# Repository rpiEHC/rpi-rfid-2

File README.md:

# RPI RFID

The goal of RPI RFID is to design, build and test an RPI id card (HID Proxcard II) reader.

## Getting Started

After cloning the repo, execute the following commands to get all the libraries we use for the project.

`git submodule init` 
`git submodule update`

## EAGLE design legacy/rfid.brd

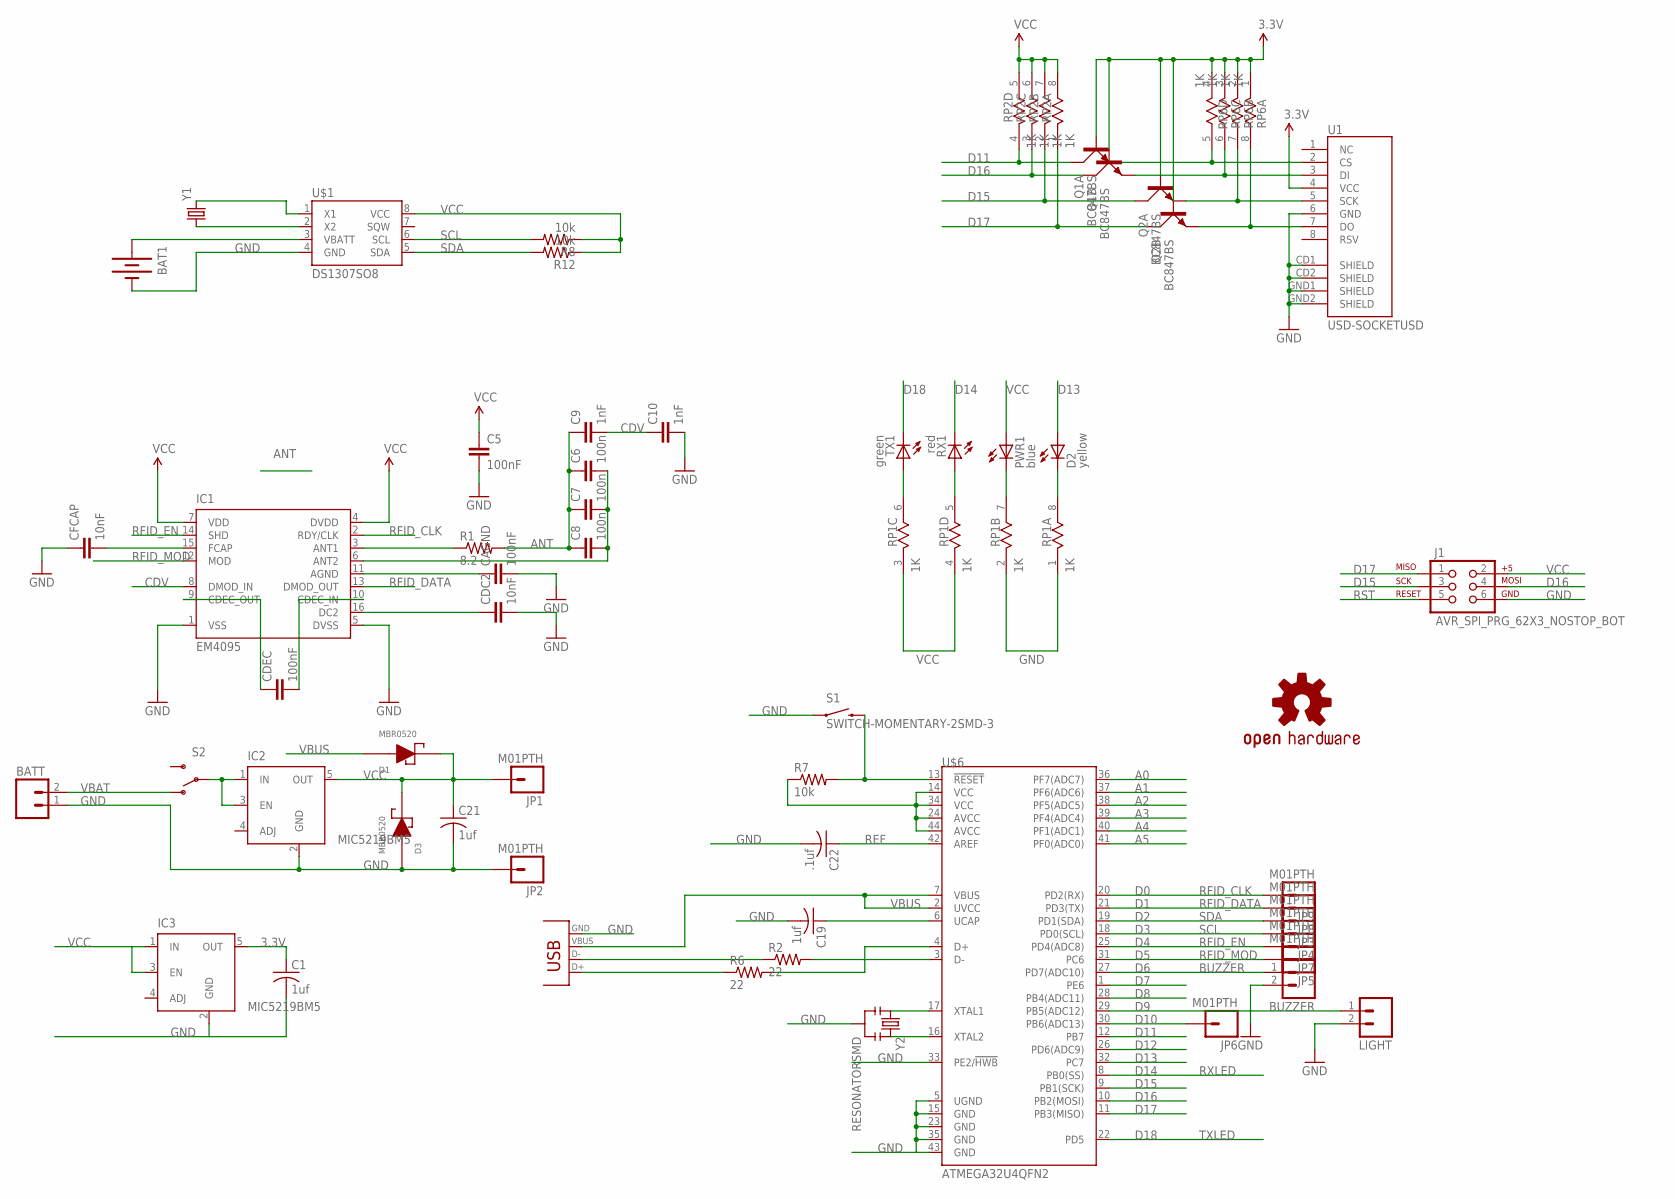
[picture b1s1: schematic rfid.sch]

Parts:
BAT1: BATTERY12MM; BATTCON_12MM
BATT: M02PTH; 1X02
BUZZER: M02PTH; 1X02
C1, C19, C21: 1uf; C0603
C5: 100nF; 0805
C6, C7, C8: 100n; 0805
C9, C10: 1nF; 0805
C22: .1uf; C0603
CAGND: 100nF; 0805
CDC2: 10nF; 0805
CDEC: 100nF; 0805
CFCAP: 10nF; 0805
D1, D3: MBR0520; SOD-123
D2: yellow; LED3MM
IC1: EM4095; SO16
IC2: MIC5219BM5; SOT23-5
IC3: MIC5219BM5; SOT23-5; MPN MIC5219BM5 TR
J1: AVR_SPI_PRG_62X3_NOSTOP_BOT; 2X3_STOP_BOT
JP1, JP2, JP3, JP4, JP5, JP6, JP7, JP8, JP9: M01PTH; 1X01
LIGHT: M02PTH; 1X02
PWR1: blue; LED3MM
Q1, Q2: BC847BS; SOT363_PHILIPS
R1: 8.2; 0805
R2, R6: 22; 0603-RES
R7, R8, R12: 10k; 0603-RES
RP1, RP2, RP6: 1K; RES4NT
RX1: red; LED3MM
S1: SWITCH-MOMENTARY-2SMD-3; TACTILE_SWITCH_SMD-3
S2: SWITCH-SPDT-SMD-A; SWITCH-SPST-SMD-A
TX1: green; LED3MM
U1: USD-SOCKETUSD; USD-SOCKET-PP
U$1: DS1307SO8; SO08
U$2: USB_MICROB; USB-MICROB
U$3: OSHW-LOGOL; OSHW-LOGO-L
U$6: ATMEGA32U4QFN2; QFN-44-NOPAD
Y1: CRYSTAL5X2; CRYSTAL-SMD-5X2
Y2: RESONATORSMD; RESONATOR-SMD

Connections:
3.3V: C1.1, IC3.5 (OUT), Q1.2 (B), Q1.5 (B), Q2.2 (B), Q2.5 (B), RP6.1, RP6.2 (1), RP6.3 (1), RP6.4 (1), U1.4 (VCC)
A0: U$6.36 (PF7(ADC7))
A1: U$6.37 (PF6(ADC6))
A2: U$6.38 (PF5(ADC5))
A3: U$6.39 (PF4(ADC4))
A4: U$6.40 (PF1(ADC1))
A5: U$6.41 (PF0(ADC0))
ANT: C6.1, C7.1, C8.1, C9.1, R1.2
CDV: C9.2, C10.1, IC1.8 (DMOD_IN)
D6: BUZZER.1, U$6.27 (PD7(ADC10))
D7: U$6.1 (PE6)
D8: U$6.28 (PB4(ADC11))
D9: LIGHT.1, U$6.29 (PB5(ADC12))
D10: JP6.1, U$6.30 (PB6(ADC13))
D11: Q1.6 (C), RP2.4 (1), U$6.12 (PB7)
D12: U$6.26 (PD6(ADC9))
D13: D2.A, U$6.32 (PC7)
D14: RX1.K (C), U$6.8 (PB0(SS))
D15: J1.3, Q2.6 (C), RP2.2 (1), U$6.9 (PB1(SCK))
D16: J1.4, Q1.3 (C), RP2.3 (1), U$6.10 (PB2(MOSI))
D17: J1.1, Q2.3 (C), RP2.1, U$6.11 (PB3(MISO))
D18: TX1.K (C), U$6.22 (PD5)
GND: BAT1.GND (-), BATT.1, BUZZER.2, C1.2, C5.2, C10.2, C19.2, C21.2, C22.2, CAGND.2, CDC2.2, CFCAP.1, D3.2 (AN), IC1.1 (VSS), IC1.5 (DVSS), IC2.2 (GND), IC3.2 (GND), J1.6, JP2.1, LIGHT.2, RP1.1, RP1.2 (1), S1.P$1 (1), U1.6 (GND), U1.CD1 (SHIELD), U1.CD2 (SHIELD), U1.GND1 (SHIELD), U1.GND2 (SHIELD), U$1.4 (GND), U$2.P4, U$2.P5, U$2.P$1, U$2.P$2, U$2.P$3, U$2.P$4, U$2.P$5, U$2.P$6, U$6.5 (UGND), U$6.15 (GND), U$6.23 (GND), U$6.33 (PE2/!HWB), U$6.35 (GND), U$6.43 (GND), Y2.2
unnamed: IC1.3 (ANT1), R1.1
unnamed: IC2.1 (IN), IC2.3 (EN), S2.2
unnamed: U$6.16 (XTAL2), Y2.3
unnamed: C6.2, C7.2, C8.2, IC1.6 (ANT2)
unnamed: Q1.4 (E), RP6.6 (2), U1.3 (DI)
unnamed: CAGND.1, IC1.11 (AGND)
unnamed: CDEC.2, IC1.10 (CDEC_IN)
unnamed: CDEC.1, IC1.9 (CDEC_OUT)
unnamed: Q2.1 (E), RP6.7 (2), U1.5 (SCK)
unnamed: Q2.4 (E), RP6.8 (2), U1.7 (DO)
unnamed: CDC2.1, IC1.16 (DC2)
unnamed: CFCAP.2, IC1.15 (FCAP)
unnamed: U$1.1 (X1), Y1.2
unnamed: U$6.17 (XTAL1), Y2.1
unnamed: U$1.2 (X2), Y1.1
unnamed: BAT1.PWR@1 (+), U$1.3 (VBATT)
unnamed: R6.2, U$6.4 (D+)
unnamed: R2.2, U$6.3 (D-)
unnamed: C19.1, U$6.6 (UCAP)
unnamed: R2.1, U$2.P2
unnamed: R6.1, U$2.P3
unnamed: RP1.6 (2), TX1.A
unnamed: RP1.5 (2), RX1.A
unnamed: PWR1.K (C), RP1.7 (2)
unnamed: D2.K (C), RP1.8 (2)
unnamed: Q1.1 (E), RP6.5 (2), U1.2 (CS)
REF: C22.1, U$6.42 (AREF)
RFID_CLK: IC1.2 (RDY/CLK), JP9.1, U$6.20 (PD2(RX))
RFID_DATA: IC1.13 (DMOD_OUT), JP8.1, U$6.21 (PD3(TX))
RFID_EN: IC1.14 (SHD), JP7.1, U$6.25 (PD4(ADC8))
RFID_MOD: IC1.12 (MOD), JP5.1, U$6.31 (PC6)
RST: J1.5, R7.2, S1.P$2 (2), U$6.13 (!RESET)
SCL: JP4.1, R8.2, U$1.6 (SCL), U$6.18 (PD0(SCL))
SDA: JP3.1, R12.2, U$1.5 (SDA), U$6.19 (PD1(SDA))
VBAT: BATT.2, S2.1 (O)
VBUS: D1.2 (AN), U$2.P1, U$6.2 (UVCC), U$6.7 (VBUS)
VCC: C5.1, C21.1, D1.1 (CA), D3.1 (CA), IC1.4 (DVDD), IC1.7 (VDD), IC2.5 (OUT), IC3.1 (IN), IC3.3 (EN), J1.2, JP1.1, PWR1.A, R7.1, R8.1, R12.1, RP1.3 (1), RP1.4 (1), RP2.5 (2), RP2.6 (2), RP2.7 (2), RP2.8 (2), U$1.8 (VCC), U$6.14 (VCC), U$6.24 (AVCC), U$6.34 (VCC), U$6.44 (AVCC)

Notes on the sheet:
RXLED
TXLED
BUZZER

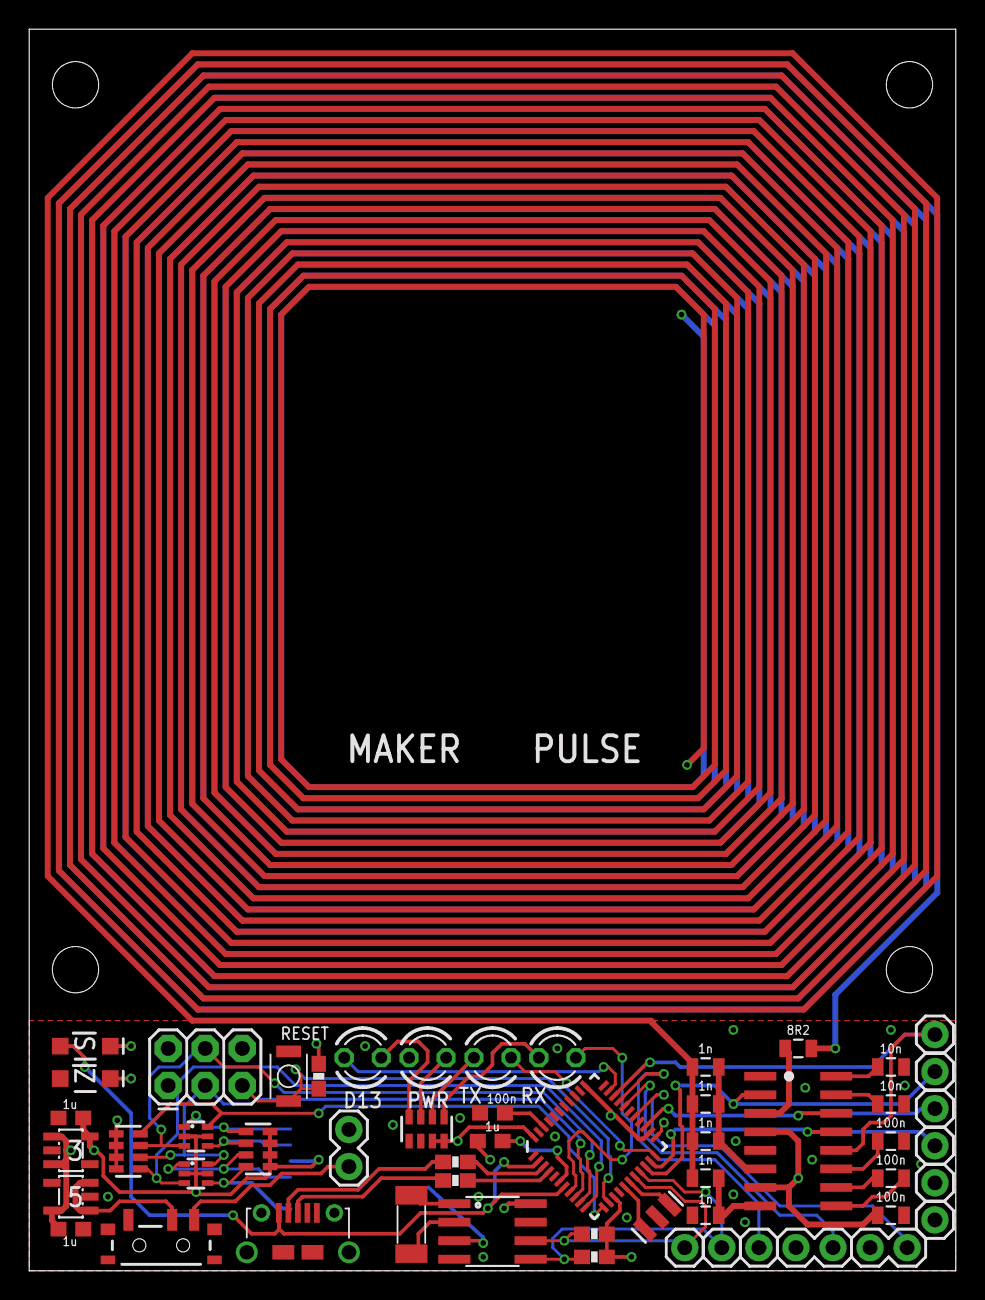
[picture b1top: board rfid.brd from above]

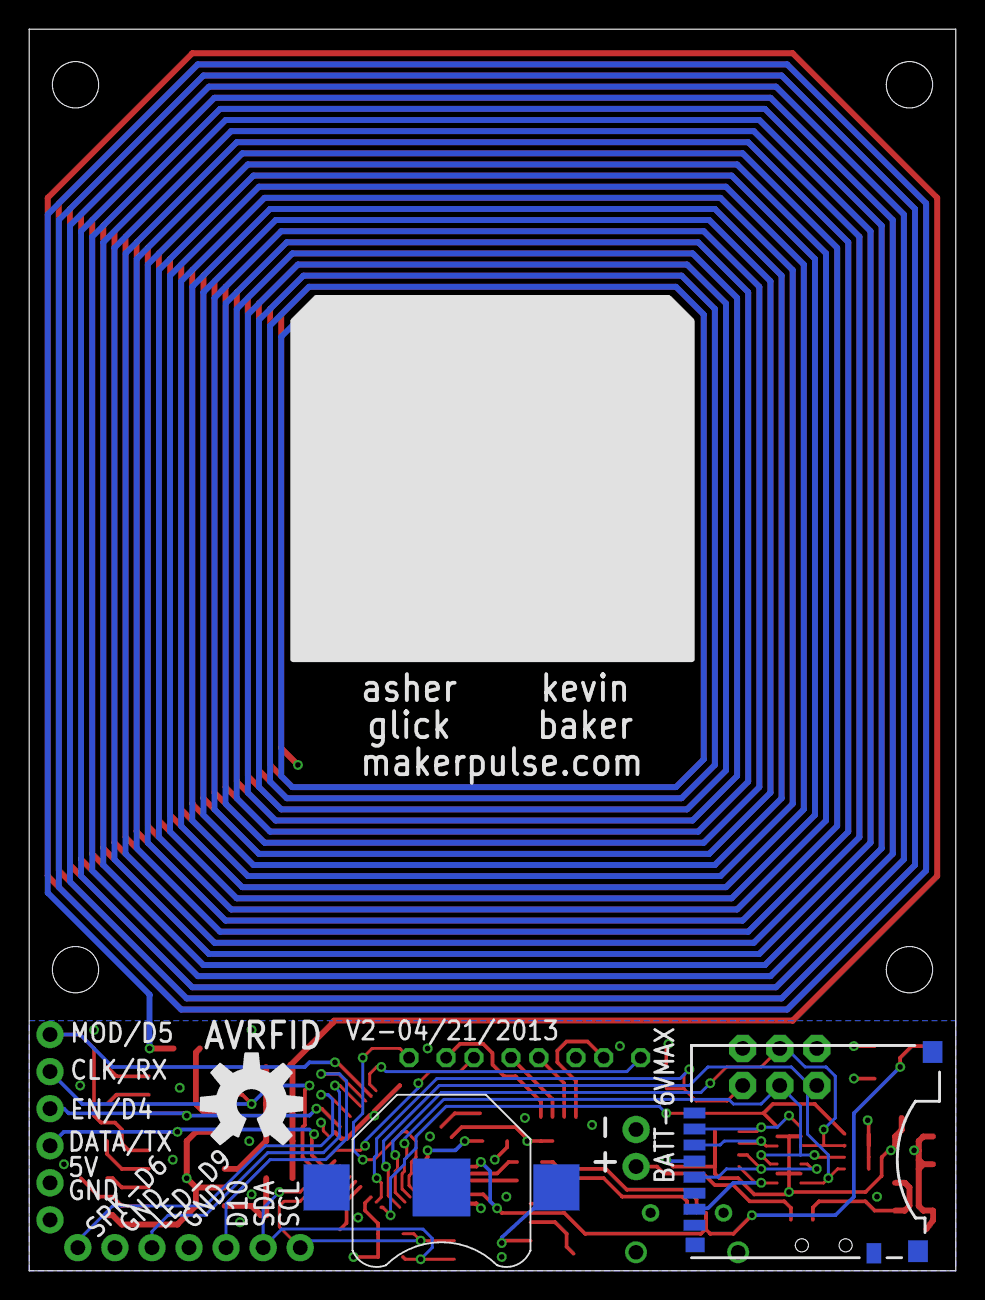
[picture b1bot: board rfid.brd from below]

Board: 4 copper layers, 63.5 x 85.1 mm, 57 parts (3 on the bottom side), 51 nets.

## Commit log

2015-09-05 initial- old eagle files
2015-09-29 added legacy files
2015-09-29 removed not "up to date" legacy eagle files
2015-10-16 Datasheets
    Datasheets for ICs in the legacy circuit
2015-10-16 More PDFs
    PDFs of the legacy board and schematic
2015-10-16 Even more PDFs and schematics & boards
    Fixed the pdf of the legacy circuit schematic
    Added reference files to the Adafruit microsdcard breakoutboard
2015-10-20 Fixed sd card eagle reference files
    Old files had some weird html stuff in it, replaced with files without
2015-10-21 initial board w/ microcontroller, programmer and usb port (in schematic)
2015-10-21 added microcontroller to datasheets directory
2015-10-30 Custom Library
    Added Part
2015-10-30 Added new component library
2015-10-30 Updated Leglamp library
    Added SD Card to library
2015-10-30 Added real time clock
2015-10-30 Revert "Added real time clock"
    This reverts commit 6b6fc6739ad60bcd637f11be7c206d4bd97eeb06.
2015-11-06 SD_Card added
2015-11-14 SD Card
    Added a Kicad circuit for the SD Card and added another schematic for
    the SD Card in the leglamp library
2015-11-14 Real time clock stuff
2015-11-20 antenna pcb
2015-11-20 added voltage regulator and antenna to schematic
2015-11-20 SD Card
    Added SD Card to the SD Card folder
2015-11-20 Removed the SD_Card circuit from the SD_Card folder
2015-11-20 em4095 module
2015-11-20 Trying to add in SD Card & SD Card Datasheet
2015-11-21 SD Card added to the main file
2015-11-21 Slight update with GND
2015-11-21 Fixed Labels and Connected SD Card to Microcontroller
2015-11-21 Fully connected SD Card and labels
2015-11-21 PCB was started
2015-12-03 created last footprint schematics
2015-12-04 added hex buffer
2015-12-05 corrected name of hex buffer
2015-12-05 SO16 component
2015-12-05 small outline 16
2015-12-05 dip8 comp
2015-12-05 new stuff
2015-12-11 added git submodule for kicad library
2015-12-11 ignore the added submodule
2015-12-11 added kicad library
2015-12-11 all but sd card associated
2015-12-12 PCB layout
2015-12-20 Routing

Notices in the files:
parts and their libraries:
SparkFun-Passives: Licensing: CC v3.0 Share-Alike You are welcome to use this library for commercial purposes.
